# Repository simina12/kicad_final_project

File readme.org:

* KiCad nRF52832
** Résumé

Modélisation sous le logiciel KiCad du schematic et du PCB d'une carte à partir du SoC nRF52832.
Cette modélisation inclue les éléments listés dans un diagramme des fonctionnalités disponible juste après.

*** Diagramme des fonctionnalités

#+begin_src ditaa :exports results :file img/diagramme_fonctionnalites.png :cmdline -E
           +--------------+                               +-------------+
           |              |                               |             |
           |              |   P12                         |             |
           |     LED      +------------+          P21     |    Prog.    |
           |    P0.10     |            |       +----------+  TC2030-CTX |          
           |              |            |       |          |             |          
           |              |            |       |          |             |          
           +--------------+            |       |          +-------------+          
                                       |       |                                   
                                       |       |                                   
                                       v       v                                   
                                   +---------------+                               
  +-----------------------+        |               |                 +--------------+
  |                       |        |               |                 |              |
  |                       |        |               |                 |              |
  |   Buzzer              |        |   nRF52832    |      P0.21      |    Reset     |
  |   CPT-7502-65-SMT-TR  | P0.09  |               |<----------------+    P0.21     |
  |                       |------->|               |                 |              |
  |                       |        |               |                 |              |
  +-----------------------+        +---------------+                 +--------------+
                                       ^        ^                        
                                       |        |                        
                                       |        |                        
                                       |        |                        
           +--------------+            |        |         +-----------------+  
           |              |            |        |         |                 |  
           |              |  P0.08     |        |  P0.02  |                 |  
           |    Bouton    +------------+        +---------+   Batterie      |  
           |   MHPS2285   |                               | BAT-HLD-006-SMT |
           |              |                               |                 |
           |              |                               |                 |
           +--------------+                               +-----------------+

#+end_src

#+CAPTION: Diagramme des fonctionnalités
#+RESULTS:
[[file:img/diagramme_fonctionnalites.png]]

** Pour commencer
*** Pré-requis :
**** KiCad

Vous avez besoin du logiciel KiCad. Il est disponible à l'adresse suivante: [[https://www.kicad.org/download/]]

** Démarrage

Ouvrir les fichiers =.kicad_sch= pour le schematic et =.kicad_pcb= pour le modèle PCB.

** Outils

- KiCad

** Versions

*Dernière version stable :* 1.0

*Dernière version :* 1.0

[[../../tags][Liste des versions]]

** Auteurs
*** Responsable de projet

- PETIT Clément
- MARCHAND Pierre

*** Equipe de développement
      
- DUREL Enzo
  
** Licence

KiCad est un logiciel libre mais soumis à certaines licence qui sont listées en détail sur leur site web à la page: [[https://www.kicad.org/about/licenses/]]

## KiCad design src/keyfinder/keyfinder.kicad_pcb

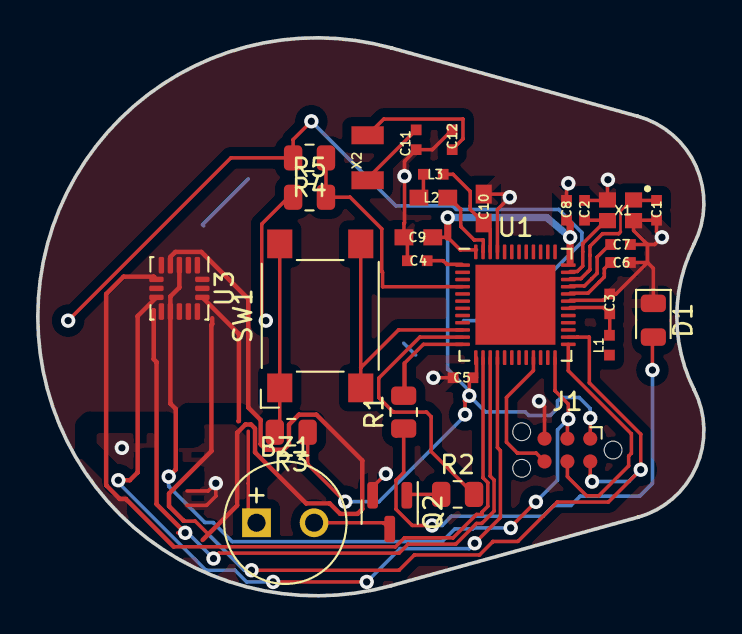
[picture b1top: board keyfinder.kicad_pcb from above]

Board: 2 copper layers, 37.0 x 31.0 mm, 30 parts (1 on the bottom side), 30 nets.

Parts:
BT1: Battery_Cell; BatteryHolder_Keystone_3034_1x20mm
BZ1: Buzzer; MagneticBuzzer_Kingstate_KCG0601
C1, C2, C11, C12: 12pF; RESC0402_N
C3: 0.8pF; RESC0402_N
C4, C5, C8: 100nF; RESC0402_N
C6: N.M.; RESC0402_N
C7: 100pF; RESC0402_N
C9: 4.7µF; RESC0603_N
C10: 1.0µF; RESC0603_N
D1: LED; LED_0805_2012Metric
J1: Conn_ARM_SWD_TagConnect_TC2030-NL; Tag-Connect_TC2030-IDC-NL_2x03_P1.27mm_Vertical
L1: 3.9nH; RESC0402_N
L2: 10µH; RESC0603_N
L3: 15nH; RESC0402_N
Q2: MMBTA42; SOT-23
R1, R2, R3, R4, R5: R; R_0805_2012Metric
SW1: SW_Push; SW_SPST_Omron_B3FS-100xP
U1: NRF52832; UQFN-48-1EP_6x6mm_P0.4mm_EP4.45x4.45mm
U3: ADXL363; Analog_LGA-16_3.25x3mm_P0.5mm_LayoutBorder3x5y
X1: 32MHz; BT-XTAL_2016_N
X2: 32.768kHz; XTAL_3215_N

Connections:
/DEC1: C4.1, U1.1 (DEC1@01)
/DEC2: C6.1, U1.32 (DEC2@32)
/DEC3: C7.1, U1.33 (DEC3@33)
/DEC4: C10.1, L3.2, U1.46 (DEC4@46)
/P0.08: SW1.2, U1.10 (P0.08@10)
/P0.09: R2.2, U1.11 (P0.09/NFC1@11)
/P0.10: R1.2, U1.12 (P0.10/NFC2@12)
/P0.18/SWO: J1.6 (SWO), U1.21 (P0.18/SWO@21)
/P0.21/RESET: J1.3 (~RESET), U1.24 (P0.21/RESET@24), U3.3 (RES), U3.10 (RES)
/SWDCLK: J1.4 (SWCLK), U1.25 (SWDCLK@25)
CS: U1.16 (P0.13@16), U3.8 (~CS)
GND: C1.2, C2.2, C3.2, C4.2, C5.2, C6.2, C7.2, C8.2, C9.2, C10.2, C11.1, C12.1, D1.1 (K), J1.5 (GND), Q2.2 (E), U1.31 (VSS@31), U1.45 (VSS@45), U3.1 (V_{DD_I/O}), U3.9 (INT2), U3.11 (INT1), U3.12 (GND), U3.13 (GND), U3.16 (GND), X1.2, X1.4
unnamed: L2.2, L3.1
unnamed: BT1.1 (+), R4.2
unnamed: BT1.2 (-), R5.1
unnamed: BZ1.2 (+), Q2.3 (C)
unnamed: D1.2 (A), R1.1
unnamed: Q2.1 (B), R2.1
unnamed: R3.2, SW1.1
unnamed: C3.1, L1.1, U1.30 (ANT@30)
unnamed: L2.1, U1.47 (DCC@47)
unnamed: C1.1, U1.34 (XC1@34), X1.1
unnamed: C2.1, U1.35 (XC2@35), X1.3
P0.00/XL1: C11.2, X2.1
P0.01/XL2: C12.2, X2.2
P02: R4.1, R5.2, U1.4 (P0.02/AIN0@04)
SCL: J1.2 (SWDIO), U1.26 (SWDIO@26), U3.4 (SCLK)
SDA: U1.15 (P0.12@15), U3.7 (MISO)
SDO: U1.14 (P0.11@14), U3.6 (MOSI)
VCC: BZ1.1 (-), C5.1, C8.1, C9.1, J1.1 (VCC), R3.1, U1.13 (VDD@13), U1.36 (VDD@36), U1.48 (VDD@48), U3.14 (V_{S})

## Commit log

2023-12-11 firts commit of the project
2023-12-11 update2
2023-12-11 final version
2023-12-11 final2 version
